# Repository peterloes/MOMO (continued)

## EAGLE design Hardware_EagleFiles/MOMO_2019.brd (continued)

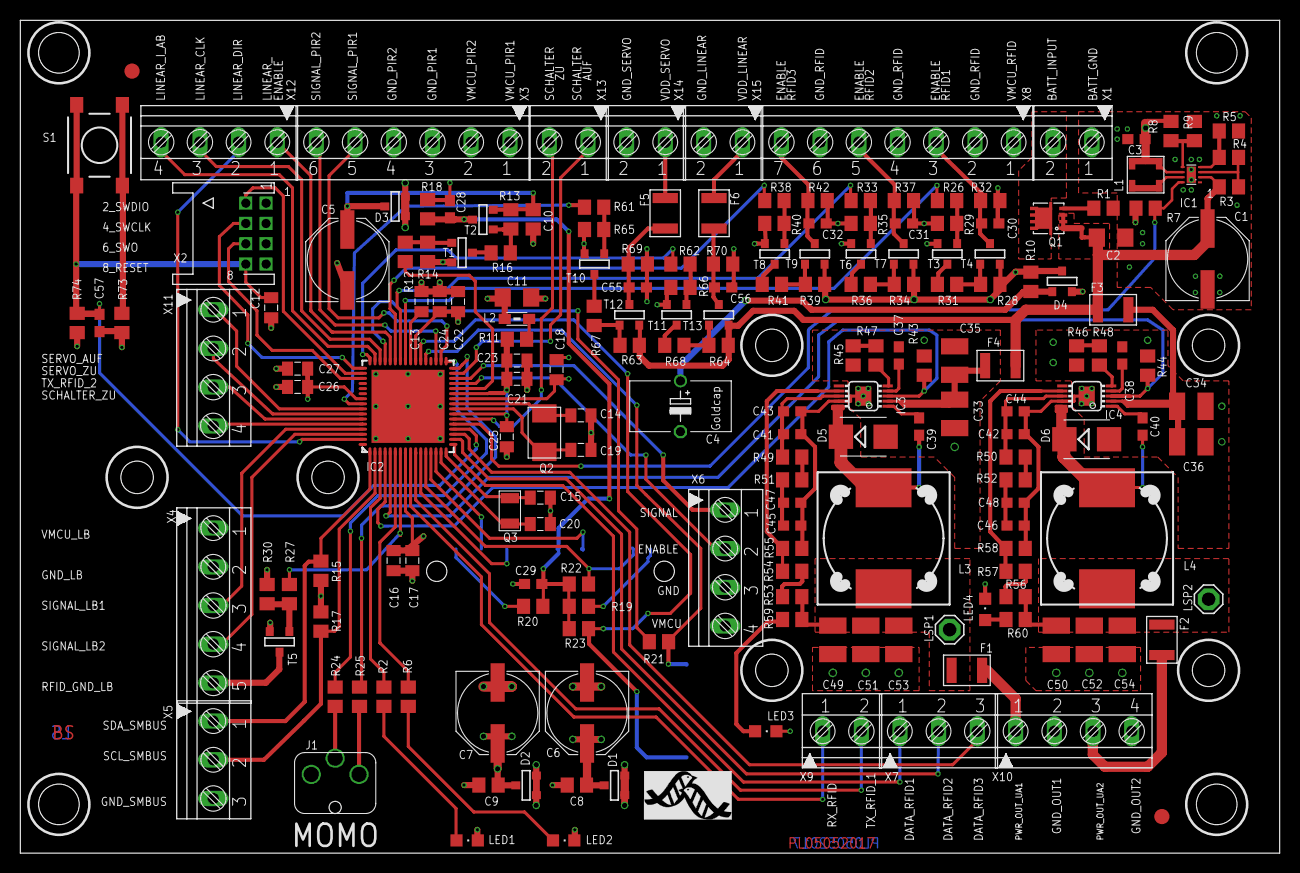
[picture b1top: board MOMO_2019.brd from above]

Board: 4 copper layers, 124.0 x 82.0 mm, 192 parts (1 on the bottom side), 132 nets.

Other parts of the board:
U$2: MPIO-ICON

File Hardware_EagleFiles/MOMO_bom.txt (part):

Partlist exported from C:/MPIO/TECHNIK/HARDWARE/EAGLE_FILES/Serenity_2015/MOMO_2_elatec.sch at 5/22/2017 10:02:44 AM

Part  Value                 Device                  Package                Description                                                    MF MPN     OC_FARNELL OC_NEWARK PACKAGE  SUPPLIER         
C1    100µF/25V             CPOL-EUE                PANASONIC_E            POLARIZED CAPACITOR, European symbol                                                                                     
C2    10µF/25V              C-EUC1206               C1206                  CAPACITOR, European symbol                                                                                               
C3    22µF/10V              C-EUC0603               C0603                  CAPACITOR, European symbol                                                                                               
C4    EECS0HD 224;Panasonic GOLDCAPSPK-V            GOLDCAPSPK-V                                                                                                                                    
C5    100µF/25V             CPOL-EUE                PANASONIC_E            POLARIZED CAPACITOR, European symbol                                                                                     
C6    100µF/25V             CPOL-EUE                PANASONIC_E            POLARIZED CAPACITOR, European symbol                                                                                     
C7    100µF/25V             CPOL-EUE                PANASONIC_E            POLARIZED CAPACITOR, European symbol                                                                                     
C8    100nF/16V             C-EUC0805               C0805                  CAPACITOR, European symbol                                                                                               
C9    100nF/16V             C-EUC0805               C0805                  CAPACITOR, European symbol                                                                                               
C10   100nF/16V             C-EUC0805               C0805                  CAPACITOR, European symbol                                                                                               
C11   10µ/25V               C-EUC1206               C1206                  CAPACITOR, European symbol                                                                                               
C12   100n                  C_SMD0805               0805                                                                                                                                            
C13   1u                    C_SMD0805               0805                                                                                                                                            
C14   12p                   C_SMD0805               0805                                                                                                                                            
C15   18p                   C_SMD0805               0805                                                                                                                                            
C16   100n                  C_SMD0805               0805                                                                                                                                            
C17   100n                  C_SMD0805               0805                                                                                                                                            
C18   100n                  C_SMD0805               0805                                                                                                                                            
C19   12p                   C_SMD0805               0805                                                                                                                                            
C20   18p                   C_SMD0805               0805                                                                                                                                            
C21   10µ                   C_SMD0805               0805                                                                                                                                            
C22   100n                  C_SMD0805               0805                                                                                                                                            
C23   100n                  C_SMD0805               0805                                                                                                                                            
C24   100n                  C_SMD0805               0805                                                                                                                                            
C25   100n                  C_SMD0805               0805                                                                                                                                            
C26   100n                  C_SMD0805               0805                                                                                                                                            
C27   10µ                   C_SMD0805               0805                                                                                                                                            
C28   100nF                 C-EUC0603               C0603                  CAPACITOR, European symbol                                                                                               
C29   100nF                 C-EUC0603               C0603                  CAPACITOR, European symbol                                                                                               
C30   100nF                 C-EUC0603               C0603                  CAPACITOR, European symbol                                                                                               
C31   100nF                 C-EUC0603               C0603                  CAPACITOR, European symbol                                                                                               
C32   100nF                 C-EUC0603               C0603                  CAPACITOR, European symbol                                                                                               
C33   4.7µF                 C-EUC1210               C1210                  CAPACITOR, European symbol                                                                                               
C34   4.7µF                 C-EUC1210               C1210                  CAPACITOR, European symbol                                                                                               
C35   n.b.                  C-EUC1210               C1210                  CAPACITOR, European symbol                                                                                               
C36   n.b.                  C-EUC1210               C1210                  CAPACITOR, European symbol                                                                                               
C37   10nF                  C-EUC0603               C0603                  CAPACITOR, European symbol                                                                                               
C38   10nF                  C-EUC0603               C0603                  CAPACITOR, European symbol                                                                                               
C39   100nF                 C-EUC0603               C0603                  CAPACITOR, European symbol                                                                                               
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
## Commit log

2019-09-30 Update README.md
    Lotte
